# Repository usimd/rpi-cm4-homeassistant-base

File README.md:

Lean Raspberry Pi CM4 base for Homeassistant
===

This is a base board for Raspberry Pi Compute Module 4 targeted for use as [Homeassistant](http://homeassistant.io/) server.

## Features

* a M.2 M-key port for NVMe (form factors 2230 and 2242 drills are available)
* an included energy meter to measure the server's power consumption
* two temperature sensors (both front and back to cover CM4 and NVMe)
* USB PD support
* ZigBee/Thread/Matter support via Silicon Labs MGM210P "Mighty Gecko" wireless module (same as used in Homeassistant Yellow)
* external antenna support for wireless module to increase transmission performance

## Requirements

* 15V USB PD compatible power supply (USB-C connector)
* 2230 or 2242 M-key NVMe module (or a CM4 with internal eMMC memory)
* (optional) equipment to flash the USB PD controller firmware residing in internal EEPROM (for instance USB-I2C adapter)

## Description

This module only exposes very few interfaces of the compute module to save on board space and keep BOM small.
If a more complete access to the device with more features included is required,
[Homeassistant Yellow](https://www.crowdsupply.com/nabu-casa/home-assistant-yellow) might be worth a look.

This base only features two USB 2.0 ports (for easy extension of other hardware like a Bluetooth dongle, external memory, etc.),
a M.2 NVMe interface to get a fast storage to run Homeassistant's database on and some monitoring devices.

Since many users want to have an overview over devices' power consumption in their setup, a energy meter is
observing the power consumed by the CM4 and the additional M.2 card. Together with two temperature sensors
and the Pi's internal sensors, the device's health state can be neatly captured and visualized in Homeassistant.

The sensors are all using a I2C protocol which is translated to the CM4 `SPI0` using a NXP
[SC18IS604](https://www.nxp.com/products/peripherals-and-logic/signal-chain/bridges/spi-to-ic-bus-bridge:SC18IS604)
bridge. That way only one internal bus is used and others are free for possible future extensions.

## Power supply and PD controller

To supply enough power to the CM4 and the NVMe SSD, a USB PD compatible power supply with 45W should be used.
Flashing the config file [tps25750_config.bin](tps25750_config.bin) to the EEPROM `U5`, the `TPS25750D` will
request 15V @ 3A max. from the power supply providing enough energy for the CM4, the NVMe SSD and external USB
devices.

The EEPROM could for instance be written using a Raspberry Pi. Connect I2C `SDA` and `SCL` pins to the Pi pins 3
and 5 respectively (i.e. `GPIO2` and `GPIO3`). Also power the base board from the Pi via USB.

Once I2C is activated on the Pi, create a new EEPROM device

```
echo 24c256 0x50 > sudo tee /sys/bus/i2c/devices/i2c-1/new_device
cat tps25750_config.bin > /sys/bus/i2c/devices/1-0050/eeprom
```

Check `dmesg`'s output after the first command to verify the successful creation of the EEPROM device.

## Pictures

## PCB manufacture link

The project has been prototyped at [AISLER](https://aisler.net/p/MXNUZCCB).

## License
GNU GPL v3 or newer

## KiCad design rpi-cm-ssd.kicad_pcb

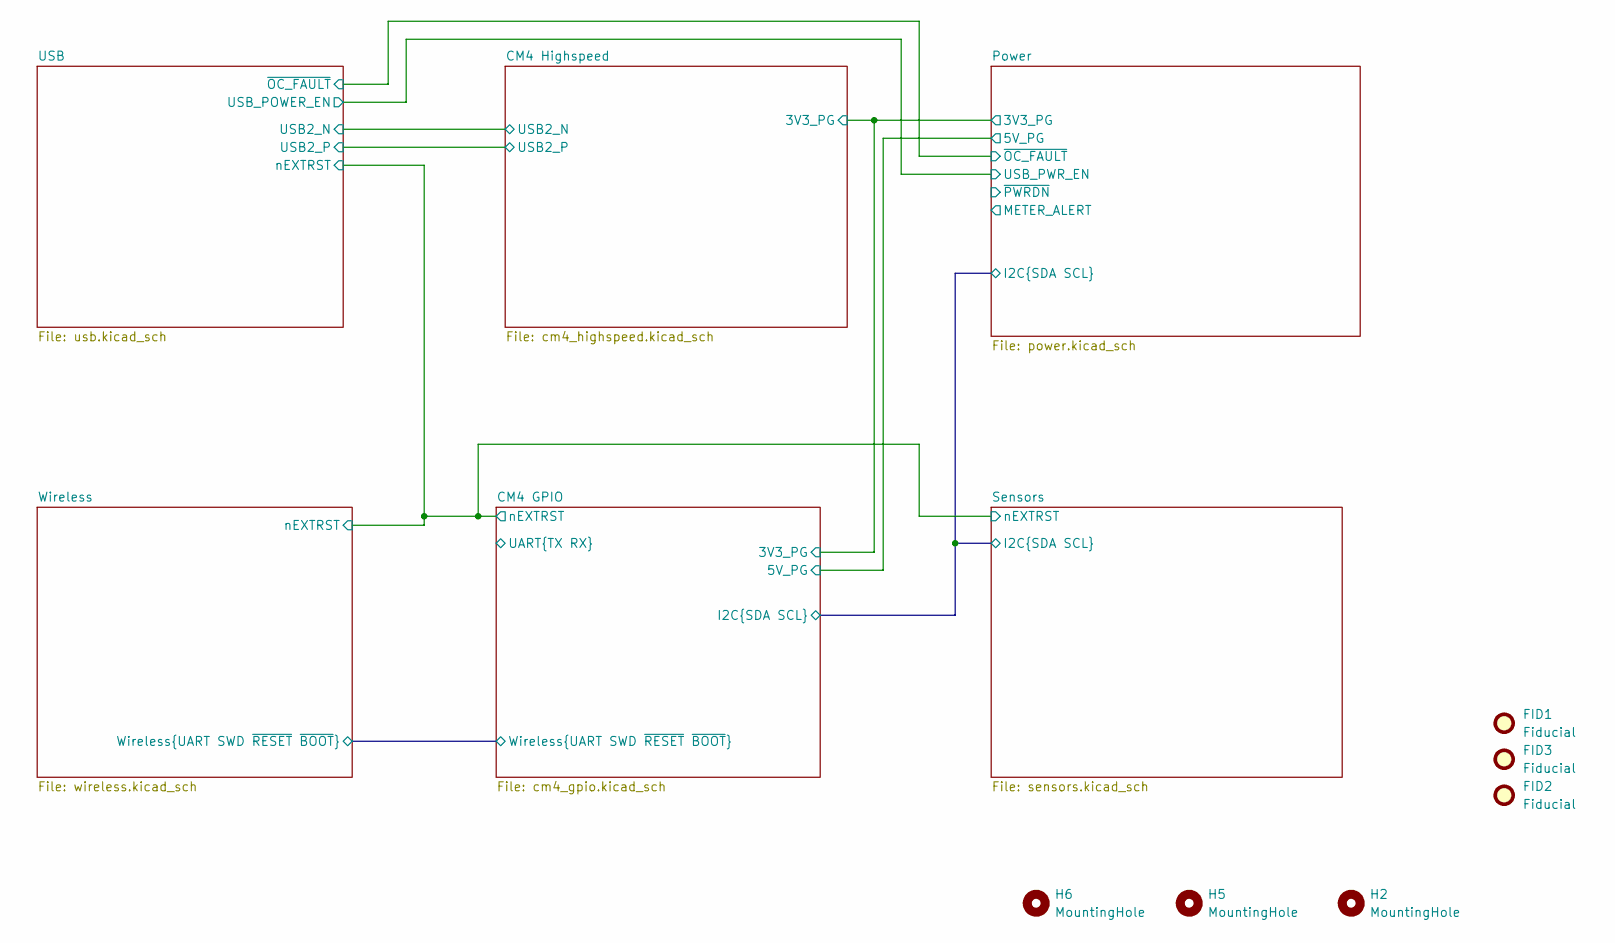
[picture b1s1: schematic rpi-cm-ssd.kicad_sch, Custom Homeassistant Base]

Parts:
FID1, FID2, FID3: Fiducial; Fiducial_0.5mm_Mask1mm
H2, H5, H6: MountingHole; MountingHole_2.7mm_M2.5; MPN KFS2-M2.5

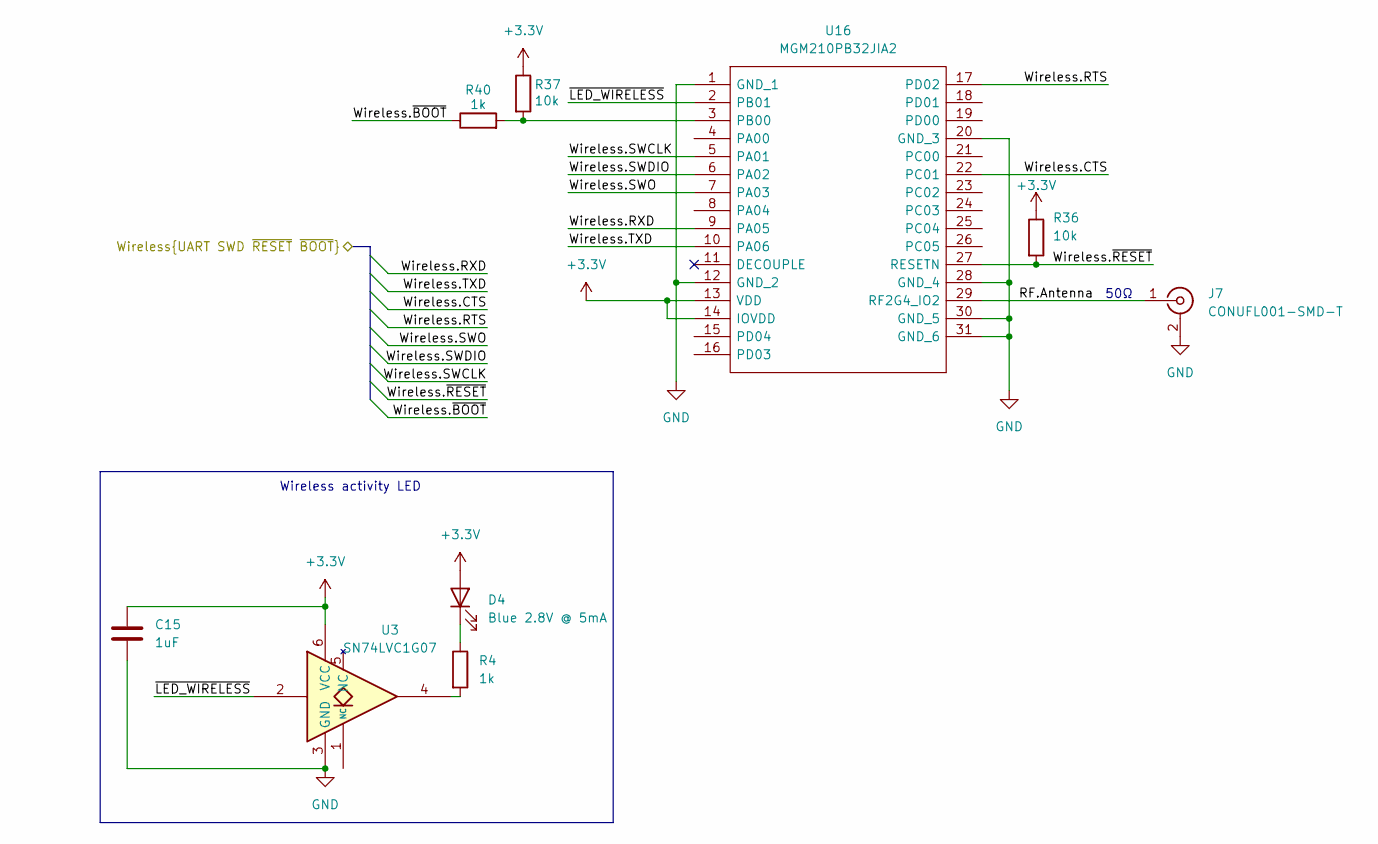
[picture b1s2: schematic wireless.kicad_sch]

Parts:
C15: 1uF; C_0402_1005Metric
D4: Blue 2.8V @ 5mA; LED_0603_1608Metric; MPN XL-1608UBC-04; LCSC Part # C965807
J7: CONUFL001-SMD-T; U.FL_Hirose_U.FL-R-SMT-1_Vertical; MPN CONUFL001-SMD-T; LCSC Part # C22418213
R4: 1k; R_0402_1005Metric
R36, R37: 10k; R_0603_1608Metric
R40: 1k; R_0603_1608Metric
U3: SN74LVC1G07; Texas_USON-6_1x1.45mm_P0.5mm_SMD; MPN SN74LVC1G07DRY; LCSC Part # C2675513
U16: MGM210PB32JIA2; MGM210PA32JIA2; Manufacturer_Part_Number MGM210PB32JIA2; Mouser Part Number 634-MGM210PB32JIA2

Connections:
+3.3V: C15.1, D4.2 (A), R36.1, R37.1, U3.6 (VCC), U16.13 (VDD), U16.14 (IOVDD); also elsewhere on the board
/CM4 GPIO/Wireless.CTS: U16.22 (PC01); also elsewhere on the board
/CM4 GPIO/Wireless.RTS: U16.17 (PD02); also elsewhere on the board
/CM4 GPIO/Wireless.RXD: U16.9 (PA05); also elsewhere on the board
/CM4 GPIO/Wireless.SWCLK: U16.5 (PA01); also elsewhere on the board
/CM4 GPIO/Wireless.SWDIO: U16.6 (PA02); also elsewhere on the board
/CM4 GPIO/Wireless.SWO: U16.7 (PA03)
/CM4 GPIO/Wireless.TXD: U16.10 (PA06); also elsewhere on the board
/CM4 GPIO/Wireless.~BOOT: R40.1; also elsewhere on the board
/CM4 GPIO/Wireless.~RESET: R36.2, U16.27 (RESETN); also elsewhere on the board
/Wireless/RF.Antenna: J7.1 (In), U16.29 (RF2G4_IO2)
/Wireless/~LED_WIRELESS: U3.2, U16.2 (PB01)
GND: C15.2, J7.2 (Ext), U3.3 (GND), U16.1 (GND_1), U16.12 (GND_2), U16.20 (GND_3), U16.28 (GND_4), U16.30 (GND_5), U16.31 (GND_6); also elsewhere on the board
unnamed: D4.1 (K), R4.1
unnamed: R4.2, U3.4
unnamed: R37.2, R40.2, U16.3 (PB00)

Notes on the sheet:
50Ω
Wireless activity LED

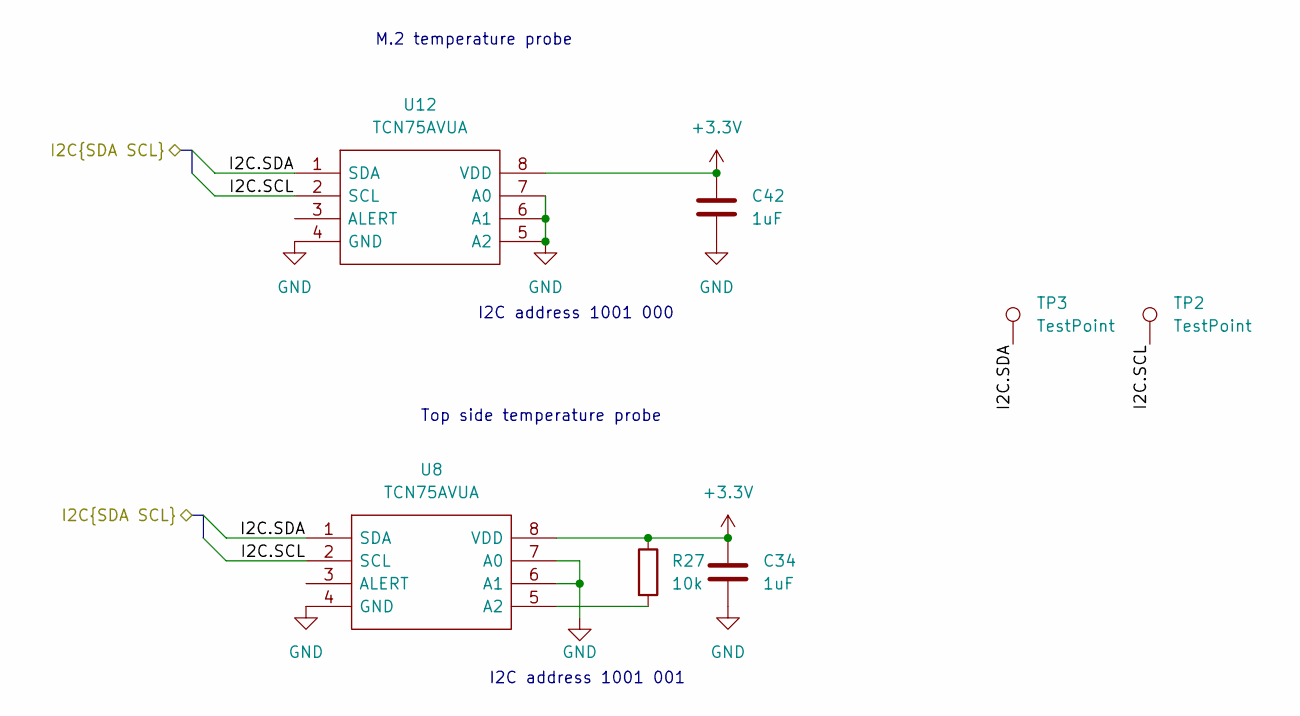
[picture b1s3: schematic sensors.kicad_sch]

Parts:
C34, C42: 1uF; C_0402_1005Metric; MPN CL05B104KA5NNNC
R27: 10k; R_0402_1005Metric; MPN AC0402FR-0710KL
TP2, TP3: TestPoint; TestPoint_Keystone_5000-5004_Miniature
U8, U12: TCN75AVUA; SOP65P490X110-8N; Manufacturer_Part_Number TCN75AVUA; Mouser Part Number 579-TCN75AVUA

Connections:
+3.3V: C34.2, C42.2, R27.1, U8.8 (VDD), U12.8 (VDD); also elsewhere on the board
/CM4 GPIO/I2C.SCL: TP2.1, U8.2 (SCL), U12.2 (SCL); also elsewhere on the board
/CM4 GPIO/I2C.SDA: TP3.1, U8.1 (SDA), U12.1 (SDA); also elsewhere on the board
GND: C34.1, C42.1, U8.4 (GND), U8.6 (A1), U8.7 (A0), U12.4 (GND), U12.5 (A2), U12.6 (A1), U12.7 (A0); also elsewhere on the board
unnamed: R27.2, U8.5 (A2)

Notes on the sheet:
M.2 temperature probe
I2C address 1001 000
Top side temperature probe
I2C address 1001 001

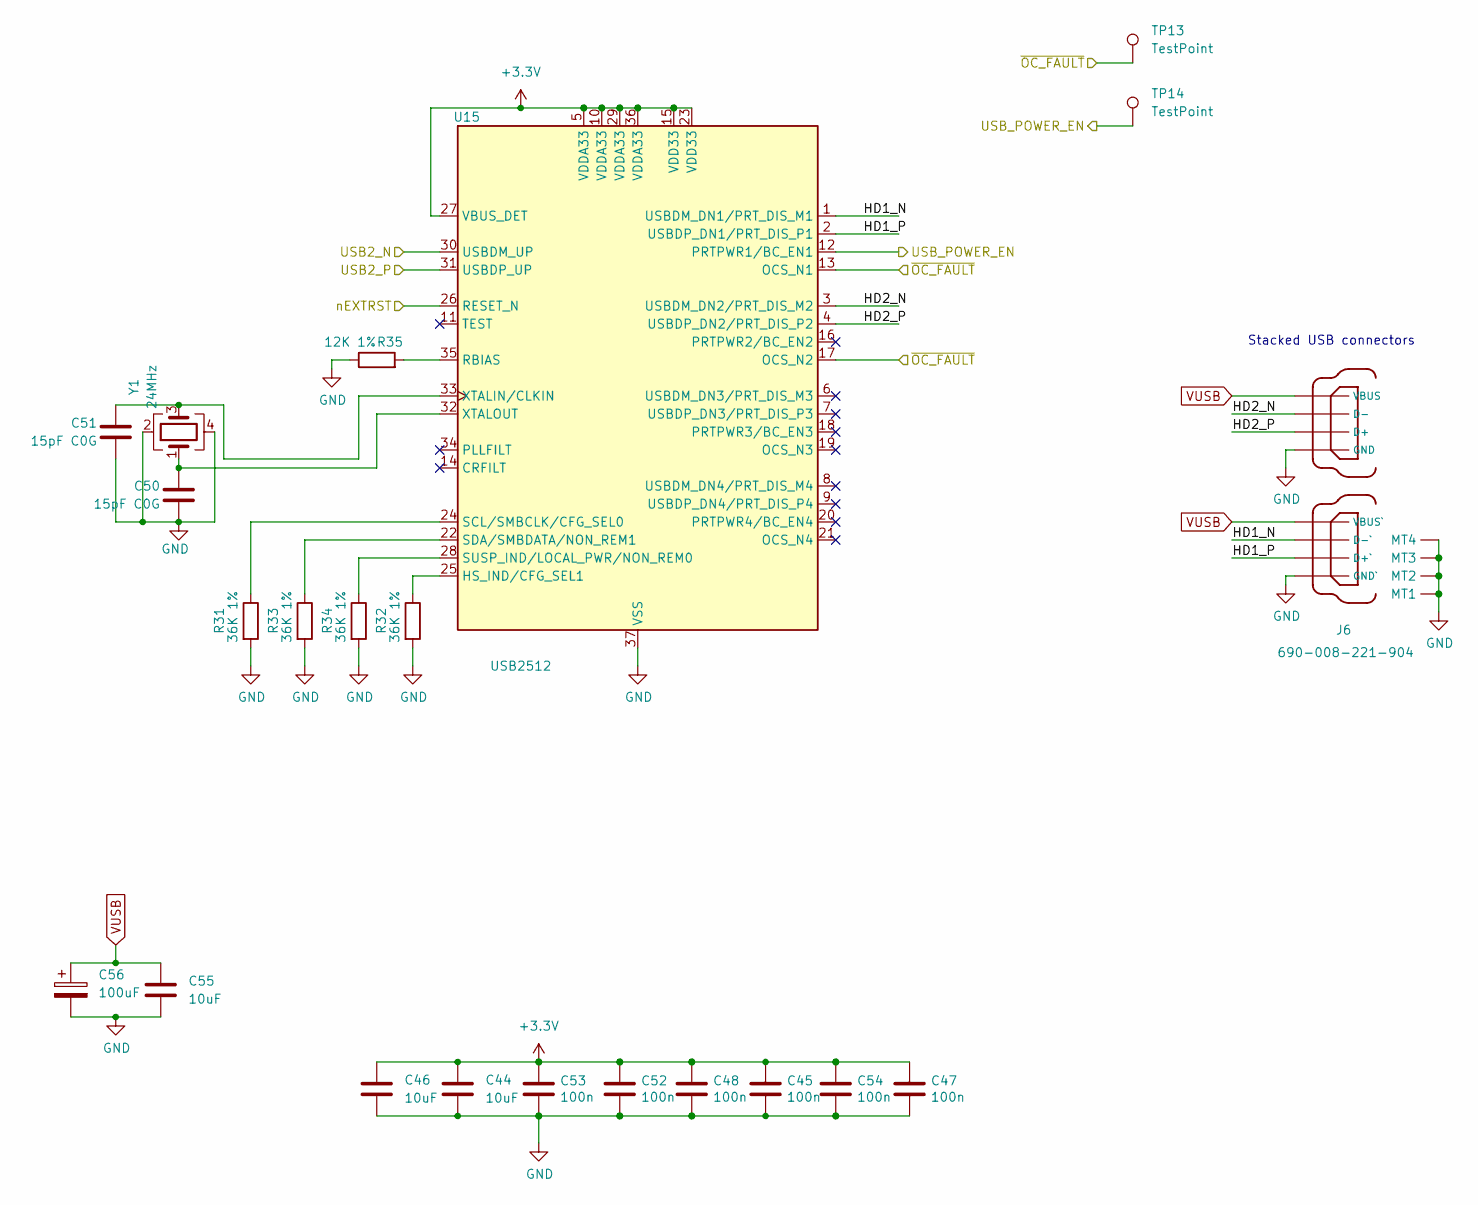
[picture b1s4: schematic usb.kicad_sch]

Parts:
C44, C46, C55: 10uF; C_0603_1608Metric; MPN GRM188R61E106KA73D
C45, C47, C48, C52, C53, C54: 100n; C_0402_1005Metric; Part Description 0.1uF 10% 16V Ceramic Capacitor X7R 040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
C50, C51: 15pF C0G; C_0402_1005Metric; MPN 04021C150KAT2A
C56: 100uF; CP_EIA-3216-10_Kemet-I
J6: 690-008-221-904; MOLEX_USB_67298-4090; Part Description USB-A (USB TYPE-A), Stacked Receptacle 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
R31, R32, R33, R34: 36K 1%; R_0402_1005Metric; Part Description Resistor 36K M1005 1% 63mW
R35: 12K 1%; R_0402_1005Metric; Part Description Resistor 12K M1005 1% 63mW
TP13, TP14: TestPoint; TestPoint_Keystone_5000-5004_Miniature
U15: USB2512; QFN-36-1EP_6x6mm_P0.5mm_EP3.7x3.7mm; Part Description USB Hub Controller USB Interface 36-SQF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; LCSC Part # C633332
Y1: 24MHz; Crystal_SMD_2520-4Pin_2.5x2.0mm; MPN ECS-240-8-36-RWN-TR3

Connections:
+3.3V: C44.2, C45.1, C46.2, C47.1, C48.1, C52.1, C53.1, C54.1, U15.5 (VDDA33), U15.10 (VDDA33), U15.15 (VDD33), U15.23 (VDD33), U15.27 (VBUS_DET), U15.29 (VDDA33), U15.36 (VDDA33); also elsewhere on the board
/CM4 GPIO/nEXTRST: U15.26 (RESET_N); also elsewhere on the board
/CM4 Highspeed/USB2_N: U15.30 (USBDM_UP); also elsewhere on the board
/CM4 Highspeed/USB2_P: U15.31 (USBDP_UP); also elsewhere on the board
/Power/USB_PWR_EN: TP14.1, U15.12 (PRTPWR1/BC_EN1); also elsewhere on the board
/Power/~OC_FAULT: TP13.1, U15.13 (OCS_N1), U15.17 (OCS_N2); also elsewhere on the board
/USB/HD1_N: J6.2 (D-`), U15.1 (USBDM_DN1/PRT_DIS_M1)
/USB/HD1_P: J6.3 (D+`), U15.2 (USBDP_DN1/PRT_DIS_P1)
/USB/HD2_N: J6.6 (D-), U15.3 (USBDM_DN2/PRT_DIS_M2)
/USB/HD2_P: J6.7 (D+), U15.4 (USBDP_DN2/PRT_DIS_P2)
GND: C44.1, C45.2, C46.1, C47.2, C48.2, C50.1, C51.1, C52.2, C53.2, C54.2, C55.1, C56.2, J6.4 (GND`), J6.8 (GND), J6.MT1, J6.MT2, J6.MT3, J6.MT4, R31.2, R32.2, R33.2, R34.2, R35.1, U15.37 (VSS), Y1.2, Y1.4; also elsewhere on the board
unnamed: R32.1, U15.25 (HS_IND/CFG_SEL1)
unnamed: R35.2, U15.35 (RBIAS)
unnamed: R31.1, U15.24 (SCL/SMBCLK/CFG_SEL0)
unnamed: R33.1, U15.22 (SDA/SMBDATA/NON_REM1)
unnamed: R34.1, U15.28 (SUSP_IND/LOCAL_PWR/NON_REM0)
unnamed: C51.2, U15.33 (XTALIN/CLKIN), Y1.3
unnamed: C50.2, U15.32 (XTALOUT), Y1.1
VUSB: C55.2, C56.1, J6.1 (VBUS`), J6.5 (VBUS); also elsewhere on the board

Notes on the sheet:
Stacked USB connectors

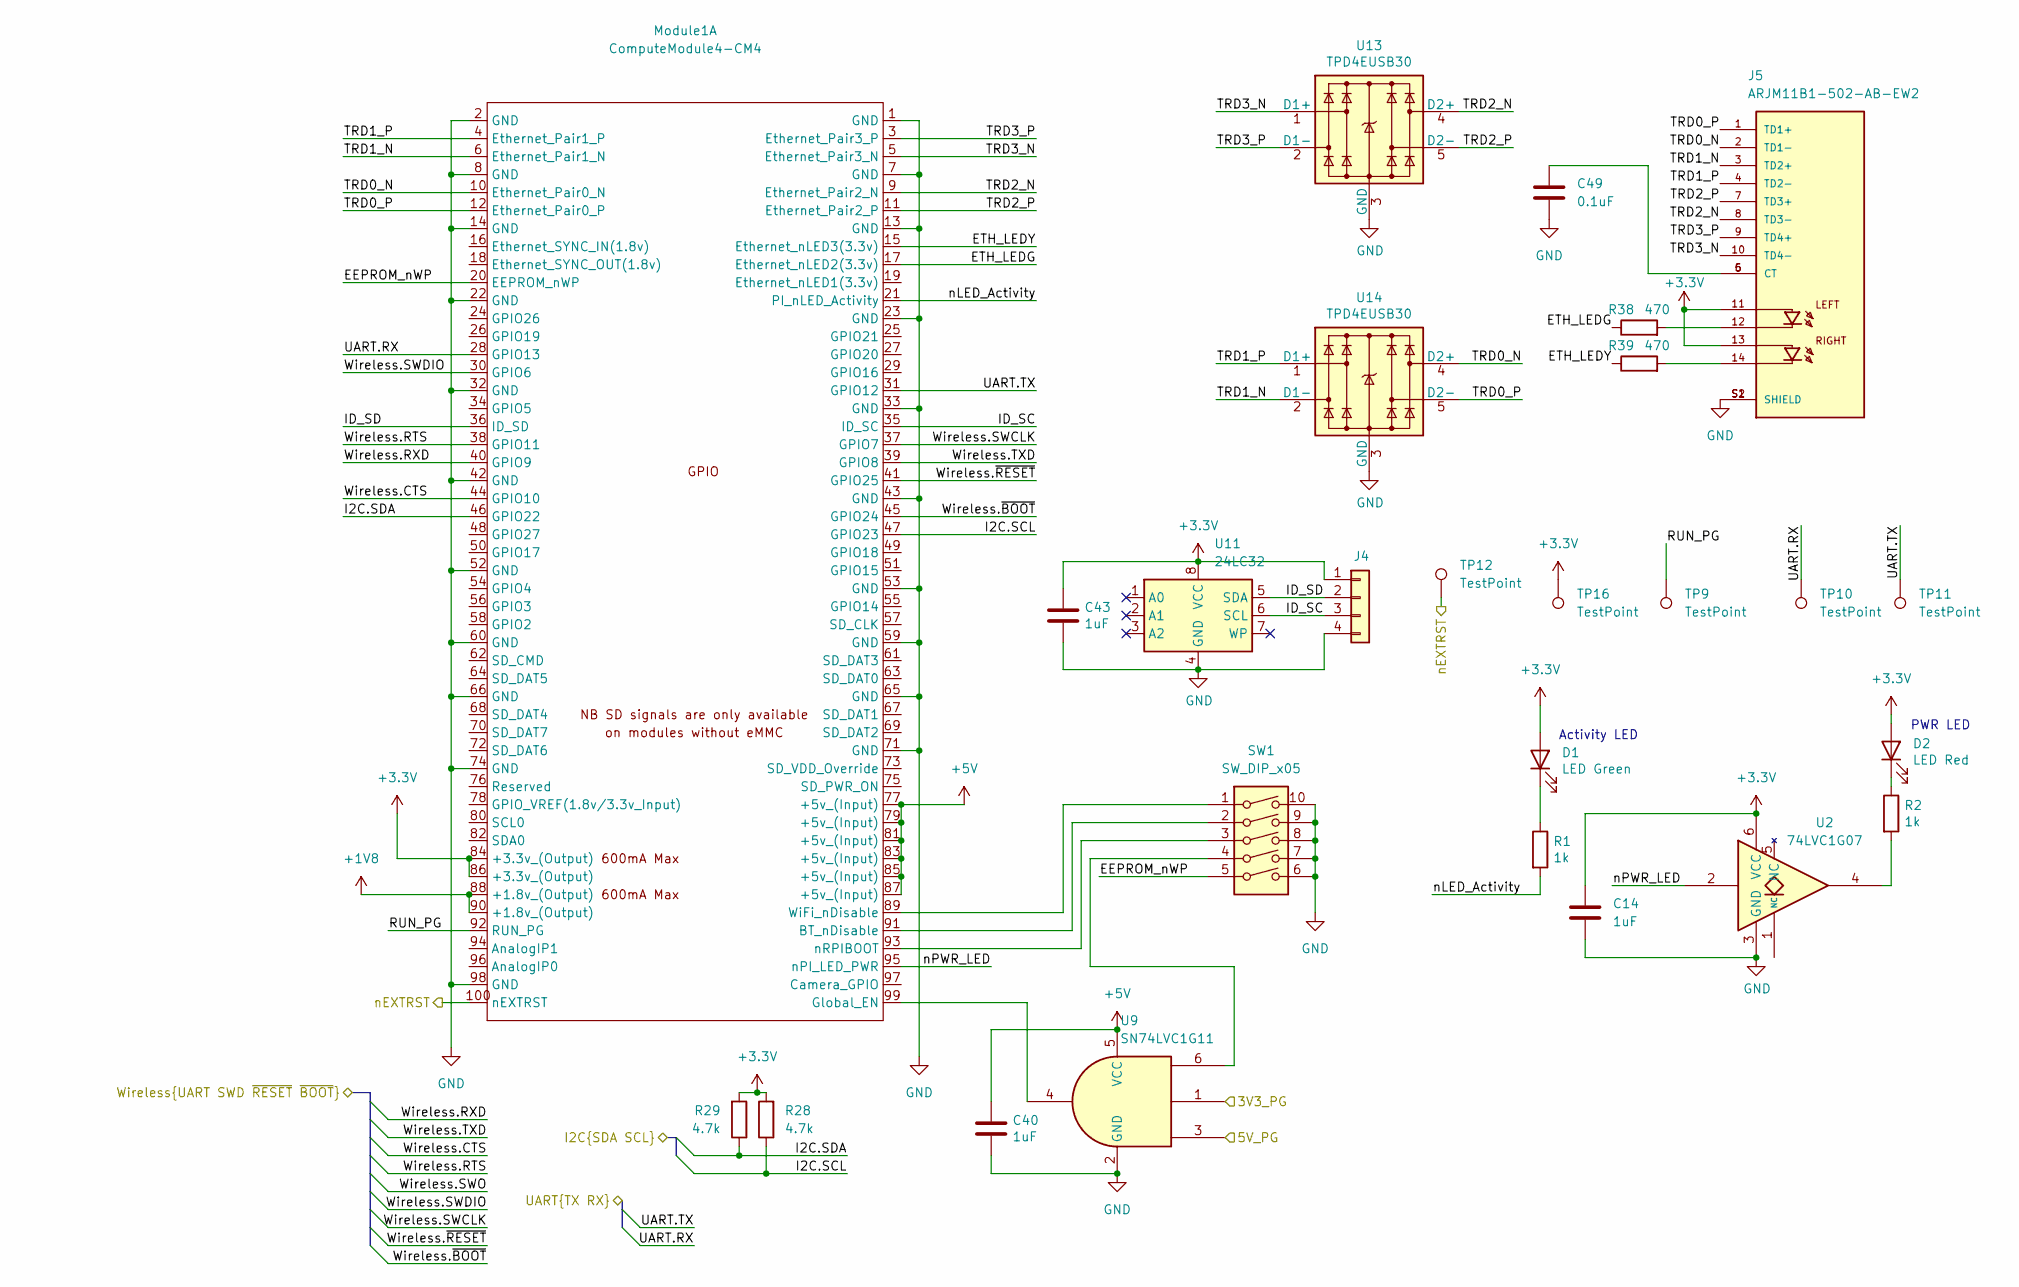
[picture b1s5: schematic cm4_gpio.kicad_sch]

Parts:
C14: 1uF; C_0402_1005Metric
C40: 1uF; C_0603_1608Metric; Part Description 0.1uF 10% 16V Ceramic Capacitor X7R 040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
C43: 1uF; C_0402_1005Metric; Part Description 0.1uF 10% 16V Ceramic Capacitor X7R 040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
C49: 0.1uF; C_0402_1005Metric; MPN CL05B104KA5NNNC
D1: LED Green; LED_0603_1608Metric; Part Description Green 572nm LED Indication - Discrete 2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; Digi-Key_PN 160-1478-1-ND
D2: LED Red; LED_0603_1608Metric; Part Description Red 620nm LED Indication - Discrete 2.2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; Digi-Key_PN 160-1479-1-ND
J4: PinHeader_1x04_P2.54mm_Vertical_SMD_Pin1Left
J5: ARJM11B1-502-AB-EW2; ABRACON_ARJM11B1-502-AB-EW2; PARTREV 01-21-20
Module1: ComputeModule4-CM4; Raspberry-Pi-4-Compute-Module; MPN DF40C-100DS-0.4V
R1, R2: 1k; R_0402_1005Metric; MPN RC0603FR-071KL; Digi-Key_PN 311-1.00KHRCT-ND
R28, R29: 4.7k; R_0402_1005Metric; MPN RC0402FR-7D4K7L
R38, R39: 470; R_0402_1005Metric; MPN RC0402FR-07470RL
SW1: SW_DIP_x05; SW_DIP_SPSTx05_Slide_KingTek_DSHP05TJ_W5.25mm_P1.27mm_JPin
TP9, TP10, TP11, TP12: TestPoint; TestPoint_Keystone_5000-5004_Miniature
TP16: TestPoint; TestPoint_Pad_D1.0mm
U2: 74LVC1G07; Texas_USON-6_1x1.45mm_P0.5mm_SMD; MPN SN74LVC1G07DRY; LCSC Part # C2675513
U9: SN74LVC1G11; Texas_USON-6_1x1.45mm_P0.5mm_SMD; MPN SN74LVC1G11DRYR
U11: 24LC32; SOIC-8_3.9x4.9mm_P1.27mm; MPN 24LC32A/SN; LCSC Part # C615215
U13, U14: TPD4EUSB30; USON-10_2.5x1.0mm_P0.5mm; Part Description Quad TVS diode for high speed signals (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; LCSC Part # C90627

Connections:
+1V8: Module1.88 (+1.8v_(Output)), Module1.90 (+1.8v_(Output))
+3.3V: C14.1, C43.1, D1.2 (A), D2.2 (A), J4.1, J5.11, J5.13, Module1.84 (+3.3v_(Output)), Module1.86 (+3.3v_(Output)), R28.2, R29.2, TP16.1, U2.6 (VCC), U11.8 (VCC); also elsewhere on the board
+5V: C40.1, Module1.77 (+5v_(Input)), Module1.79 (+5v_(Input)), Module1.81 (+5v_(Input)), Module1.83 (+5v_(Input)), Module1.85 (+5v_(Input)), Module1.87 (+5v_(Input)), U9.5 (VCC); also elsewhere on the board
/CM4 GPIO/3V3_PG: U9.1; also elsewhere on the board
/CM4 GPIO/5V_PG: U9.3; also elsewhere on the board
/CM4 GPIO/EEPROM_nWP: Module1.20 (EEPROM_nWP), SW1.5
/CM4 GPIO/ETH_LEDG: Module1.17 (Ethernet_nLED2(3.3v)), R38.1
/CM4 GPIO/ETH_LEDY: Module1.15 (Ethernet_nLED3(3.3v)), R39.1
/CM4 GPIO/I2C.SCL: Module1.47 (GPIO23), R28.1; also elsewhere on the board
/CM4 GPIO/I2C.SDA: Module1.46 (GPIO22), R29.1; also elsewhere on the board
/CM4 GPIO/ID_SC: J4.3, Module1.35 (ID_SC), U11.6 (SCL)
/CM4 GPIO/ID_SD: J4.2, Module1.36 (ID_SD), U11.5 (SDA)
/CM4 GPIO/RUN_PG: Module1.92 (RUN_PG), TP9.1
/CM4 GPIO/TRD0_N: J5.2 (TD1-), Module1.10 (Ethernet_Pair0_N), U14.4 (D2+), U14.7
/CM4 GPIO/TRD0_P: J5.1 (TD1+), Module1.12 (Ethernet_Pair0_P), U14.5 (D2-), U14.6
/CM4 GPIO/TRD1_N: J5.3 (TD2+), Module1.6 (Ethernet_Pair1_N), U14.2 (D1-), U14.9
/CM4 GPIO/TRD1_P: J5.4 (TD2-), Module1.4 (Ethernet_Pair1_P), U14.1 (D1+), U14.10
/CM4 GPIO/TRD2_N: J5.8 (TD3-), Module1.9 (Ethernet_Pair2_N), U13.4 (D2+), U13.7
/CM4 GPIO/TRD2_P: J5.7 (TD3+), Module1.11 (Ethernet_Pair2_P), U13.5 (D2-), U13.6
/CM4 GPIO/TRD3_N: J5.10 (TD4-), Module1.5 (Ethernet_Pair3_N), U13.1 (D1+), U13.10
/CM4 GPIO/TRD3_P: J5.9 (TD4+), Module1.3 (Ethernet_Pair3_P), U13.2 (D1-), U13.9
/CM4 GPIO/UART.RX: Module1.28 (GPIO13), TP10.1
/CM4 GPIO/UART.TX: Module1.31 (GPIO12), TP11.1
/CM4 GPIO/Wireless.CTS: Module1.44 (GPIO10); also elsewhere on the board
/CM4 GPIO/Wireless.RTS: Module1.38 (GPIO11); also elsewhere on the board
/CM4 GPIO/Wireless.RXD: Module1.40 (GPIO9); also elsewhere on the board
/CM4 GPIO/Wireless.SWCLK: Module1.37 (GPIO7); also elsewhere on the board
/CM4 GPIO/Wireless.SWDIO: Module1.30 (GPIO6); also elsewhere on the board
/CM4 GPIO/Wireless.TXD: Module1.39 (GPIO8); also elsewhere on the board
/CM4 GPIO/Wireless.~BOOT: Module1.45 (GPIO24); also elsewhere on the board
/CM4 GPIO/Wireless.~RESET: Module1.41 (GPIO25); also elsewhere on the board
/CM4 GPIO/nEXTRST: Module1.100 (nEXTRST), TP12.1; also elsewhere on the board
/CM4 GPIO/nLED_Activity: Module1.21 (PI_nLED_Activity), R1.2
/CM4 GPIO/nPWR_LED: Module1.95 (nPI_LED_PWR), U2.2
GND: C14.2, C40.2, C43.2, C49.2, J4.4, J5.S1 (SHIELD), J5.S2 (SHIELD), Module1.1 (GND), Module1.2 (GND), Module1.7 (GND), Module1.8 (GND), Module1.13 (GND), Module1.14 (GND), Module1.22 (GND), Module1.23 (GND), Module1.32 (GND), Module1.33 (GND), Module1.42 (GND), Module1.43 (GND), Module1.52 (GND), Module1.53 (GND), Module1.59 (GND), Module1.60 (GND), Module1.65 (GND), Module1.66 (GND), Module1.71 (GND), Module1.74 (GND), Module1.98 (GND), SW1.6, SW1.7, SW1.8, SW1.9, SW1.10, U2.3 (GND), U9.2 (GND), U11.4 (GND), U13.3 (GND), U13.8 (GND), U14.3 (GND), U14.8 (GND); also elsewhere on the board
unnamed: C49.1, J5.5 (CT), J5.6 (CT)
unnamed: D1.1 (K), R1.1
unnamed: D2.1 (K), R2.1
unnamed: J5.12, R38.2
unnamed: J5.14, R39.2
unnamed: Module1.91 (BT_nDisable), SW1.2
unnamed: Module1.99 (Global_EN), U9.4
unnamed: Module1.89 (WiFi_nDisable), SW1.1
unnamed: Module1.93 (nRPIBOOT), SW1.3
unnamed: R2.2, U2.4
unnamed: SW1.4, U9.6

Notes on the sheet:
PWR LED
Activity LED

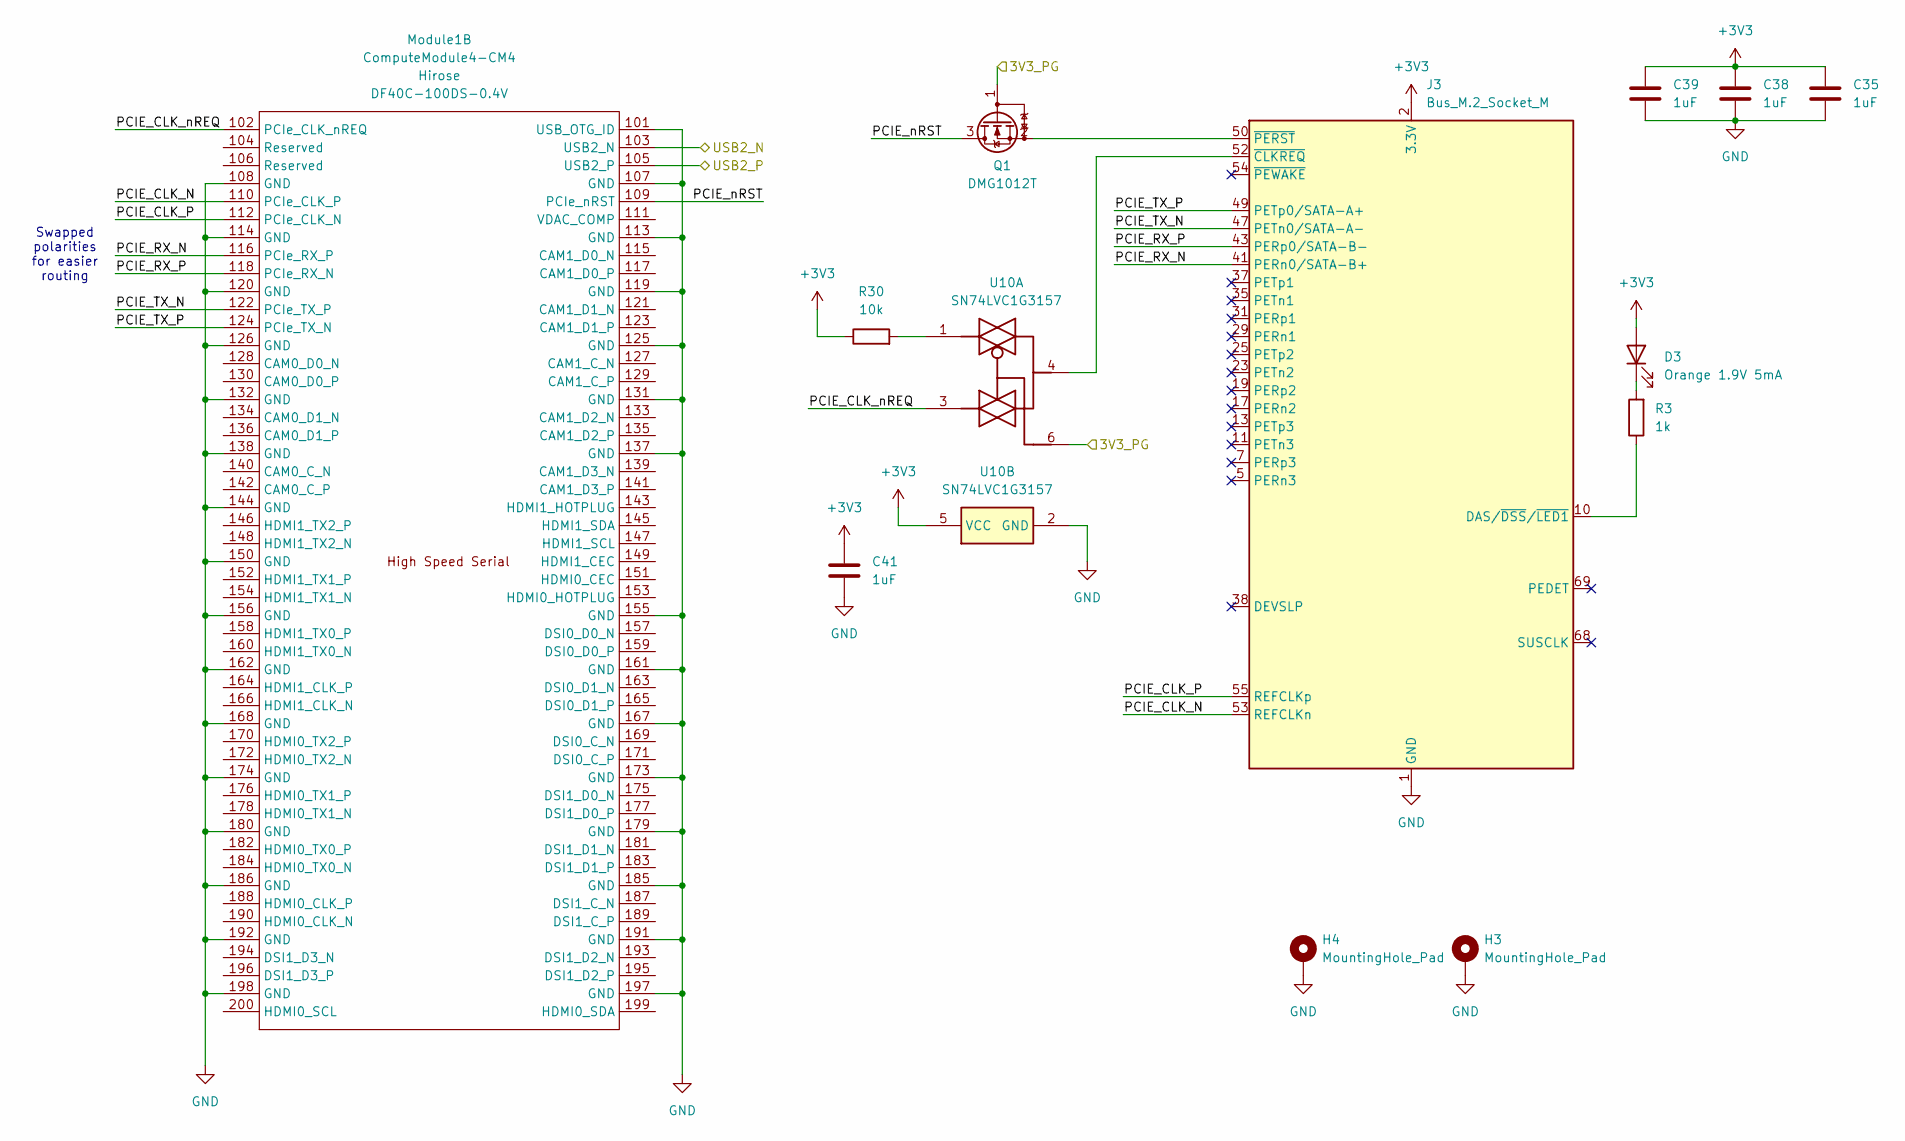
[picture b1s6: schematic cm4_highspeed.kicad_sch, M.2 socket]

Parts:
C35, C38, C39, C41: 1uF; C_0402_1005Metric
D3: Orange 1.9V 5mA; LED_0603_1608Metric; MPN HSMD-C190; LCSC Part # C18198804
H3, H4: MountingHole_Pad; MountingHole_3.7mm_Pad_TopOnly; MPN 9774015151R
J3: Bus_M.2_Socket_M; JAE_SM3ZS067U310AMR1200; MPN SM3ZS067U310AMR1200; LCSC Part # C4527433
Module1: ComputeModule4-CM4; Raspberry-Pi-4-Compute-Module; MPN DF40C-100DS-0.4V
Q1: DMG1012T; SOT-523; MPN DMG1012T-13; LCSC Part # C42412320
R3: 1k; R_0402_1005Metric
R30: 10k; R_0603_1608Metric
U10: SN74LVC1G3157; SOT-363_SC-70-6; MPN SN74LVC1G3157DRYR; LCSC Part # C2870968

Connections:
+3V3: C35.1, C38.1, C39.1, C41.1, D3.2 (A), J3.2 (3.3V), J3.4 (3.3V), J3.12 (3.3V), J3.14 (3.3V), J3.16 (3.3V), J3.18 (3.3V), J3.70 (3.3V), J3.72 (3.3V), J3.74 (3.3V), R30.1, U10.5 (VCC); also elsewhere on the board
/CM4 GPIO/3V3_PG: Q1.1 (G), U10.6; also elsewhere on the board
/CM4 Highspeed/PCIE_CLK_N: J3.53 (REFCLKn), Module1.110 (PCIe_CLK_P)
/CM4 Highspeed/PCIE_CLK_P: J3.55 (REFCLKp), Module1.112 (PCIe_CLK_N)
/CM4 Highspeed/PCIE_CLK_nREQ: Module1.102 (PCIe_CLK_nREQ), U10.3
/CM4 Highspeed/PCIE_RX_N: J3.41 (PERn0/SATA-B+), Module1.116 (PCIe_RX_P)
/CM4 Highspeed/PCIE_RX_P: J3.43 (PERp0/SATA-B-), Module1.118 (PCIe_RX_N)
/CM4 Highspeed/PCIE_TX_N: J3.47 (PETn0/SATA-A-), Module1.122 (PCIe_TX_P)
/CM4 Highspeed/PCIE_TX_P: J3.49 (PETp0/SATA-A+), Module1.124 (PCIe_TX_N)
/CM4 Highspeed/PCIE_nRST: Module1.109 (PCIe_nRST), Q1.3 (D)
/CM4 Highspeed/USB2_N: Module1.103 (USB2_N); also elsewhere on the board
/CM4 Highspeed/USB2_P: Module1.105 (USB2_P); also elsewhere on the board
GND: C35.2, C38.2, C39.2, C41.2, H3.1, H4.1, J3.1 (GND), J3.3 (GND), J3.9 (GND), J3.15 (GND), J3.21 (GND), J3.27 (GND), J3.33 (GND), J3.39 (GND), J3.45 (GND), J3.51 (GND), J3.57 (GND), J3.71 (GND), J3.73 (GND), J3.75 (GND), Module1.101 (USB_OTG_ID), Module1.107 (GND), Module1.108 (GND), Module1.113 (GND), Module1.114 (GND), Module1.119 (GND), Module1.120 (GND), Module1.125 (GND), Module1.126 (GND), Module1.131 (GND), Module1.132 (GND), Module1.137 (GND), Module1.138 (GND), Module1.144 (GND), Module1.150 (GND), Module1.155 (GND), Module1.156 (GND), Module1.161 (GND), Module1.162 (GND), Module1.167 (GND), Module1.168 (GND), Module1.173 (GND), Module1.174 (GND), Module1.179 (GND), Module1.180 (GND), Module1.185 (GND), Module1.186 (GND), Module1.191 (GND), Module1.192 (GND), Module1.197 (GND), Module1.198 (GND), U10.2 (GND); also elsewhere on the board
unnamed: D3.1 (K), R3.2
unnamed: J3.10 (DAS/~DSS/~LED1), R3.1
unnamed: J3.52 (~CLKREQ), U10.4
unnamed: J3.50 (~PERST), Q1.2 (S)
unnamed: R30.2, U10.1

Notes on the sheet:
Swapped polarities for easier routing
